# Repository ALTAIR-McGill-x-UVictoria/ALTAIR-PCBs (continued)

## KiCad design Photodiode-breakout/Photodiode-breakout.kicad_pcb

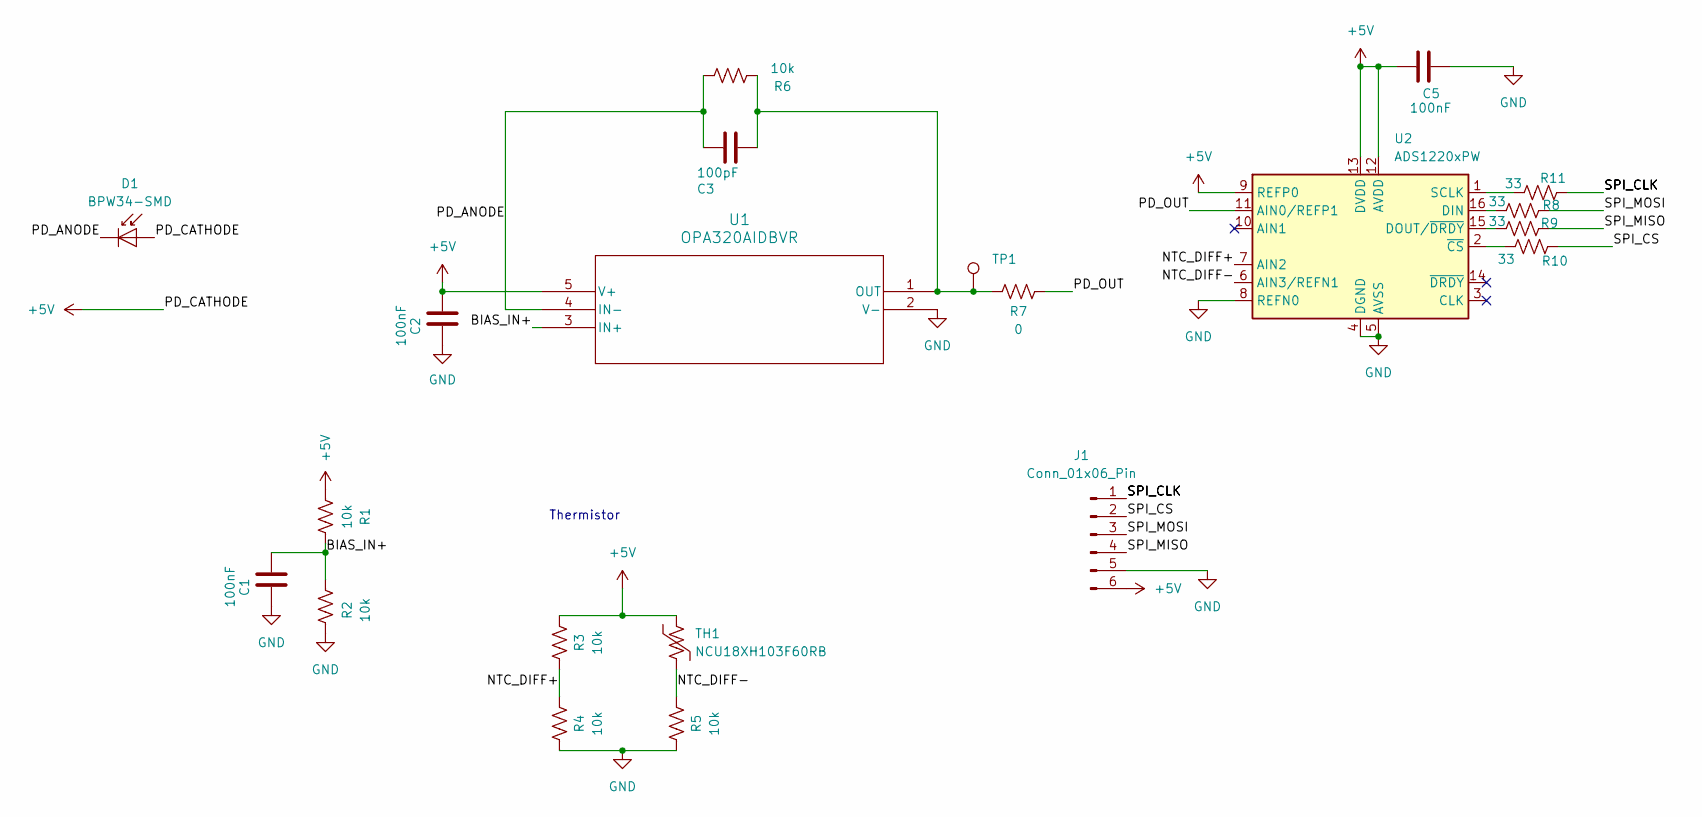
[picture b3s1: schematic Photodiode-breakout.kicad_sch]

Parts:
C1, C2, C5: 100nF; C_0603_1608Metric
C3: 100pF; C_0603_1608Metric
D1: BPW34-SMD; Osram_BPW34S-SMD
J1: Conn_01x06_Pin; JST_GH_BM06B-GHS-TBT_1x06-1MP_P1.25mm_Vertical
R1, R2, R3, R4, R5, R6: 10k; R_0603_1608Metric
R7: 0; R_0603_1608Metric
R8, R9, R10, R11: 33; R_0603_1608Metric
TH1: NCU18XH103F60RB; R_0603_1608Metric
TP1: TestPoint; PinHeader_1x01_P2.54mm_Vertical
U1: OPA320AIDBVR; DBV5
U2: ADS1220xPW; TSSOP-16_4.4x5mm_P0.65mm

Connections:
+5V: C2.1, C5.1, D1.2 (A), J1.6, R1.1, R3.2, TH1.1, U1.5 (V+), U2.9 (REFP0), U2.12 (AVDD), U2.13 (DVDD)
/BIAS_IN+: C1.1, R1.2, R2.2, U1.3 (IN+)
/NTC_DIFF+: R3.1, R4.2, U2.7 (AIN2)
/NTC_DIFF-: R5.2, TH1.2, U2.6 (AIN3/REFN1)
/PD_ANODE: C3.1, D1.1 (K), R6.2, U1.4 (IN-)
/PD_OUT: R7.2, U2.11 (AIN0/REFP1)
/SPI_CLK: J1.1, R11.1
/SPI_CS: J1.2, R10.1
/SPI_MISO: J1.4, R9.1
/SPI_MOSI: J1.3, R8.1
GND: C1.2, C2.2, C5.2, J1.5, R2.1, R4.1, R5.1, U1.2 (V-), U2.4 (DGND), U2.5 (AVSS), U2.8 (REFN0)
unnamed: C3.2, R6.1, R7.1, TP1.1 (1_1), U1.1 (OUT)
unnamed: R8.2, U2.16 (DIN)
unnamed: R9.2, U2.15 (DOUT/~DRDY)
unnamed: R11.2, U2.1 (SCLK)
unnamed: R10.2, U2.2 (~CS)

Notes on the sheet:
Thermistor

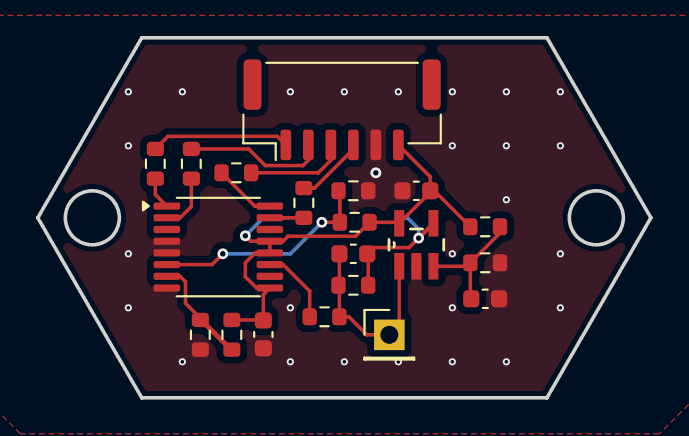
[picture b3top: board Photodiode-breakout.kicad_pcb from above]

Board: 2 copper layers, 34.1 x 20.0 mm, 21 parts (1 on the bottom side), 16 nets.

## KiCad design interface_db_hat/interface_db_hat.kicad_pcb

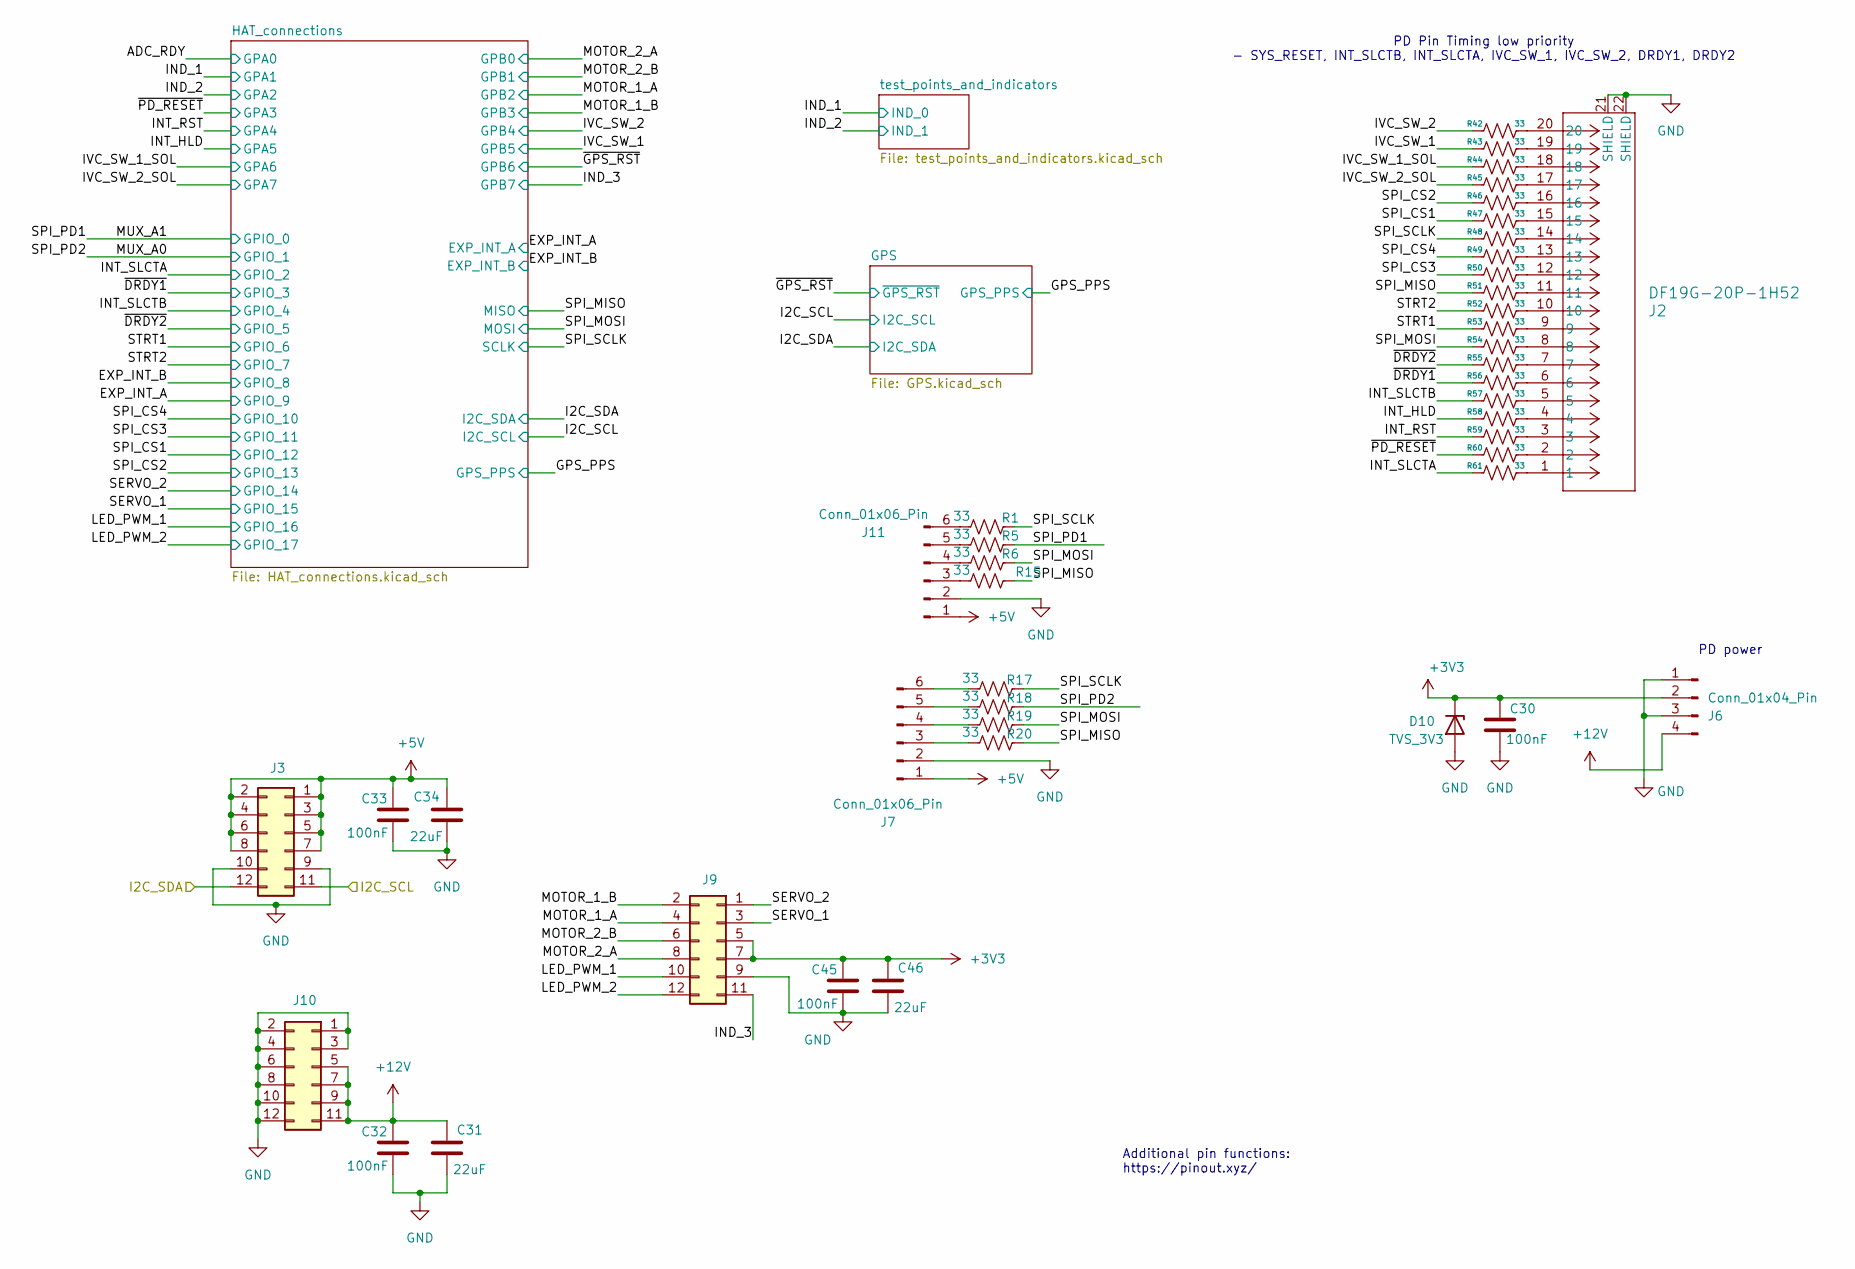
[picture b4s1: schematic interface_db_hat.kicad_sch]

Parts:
C30, C32, C33, C45: 100nF; C_0603_1608Metric_Pad1.08x0.95mm_HandSolder
C31, C34, C46: 22uF; C_0805_2012Metric
D10: TVS_3V3; D_0603_1608Metric
J2: DF19G-20P-1H52; CONN20_DF19G_HIR
J3, J9, J10: Conn_02x06_Counter_Clockwise; PinSocket_2x06_P2.54mm_Vertical
J6: Conn_01x04_Pin; JST_SH_SM04B-SRSS-TB_1x04-1MP_P1.00mm_Horizontal
J7, J11: Conn_01x06_Pin; JST_GH_SM06B-GHS-TB_1x06-1MP_P1.25mm_Horizontal
R1, R5, R6, R15, R17, R18, R19, R20: 33; R_0603_1608Metric
R42, R43, R44, R45, R46, R47, R48, R49, R50, R51, R52, R53, R54, R55, R56, R57, R58, R59, R60, R61: 33; R_0603_1608Metric_Pad0.98x0.95mm_HandSolder

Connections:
+3V3: C30.1, C45.2, C46.1, D10.1 (K), J6.2, J9.5, J9.7; also elsewhere on the board
+5V: C33.2, C34.1, J3.1, J3.2, J3.3, J3.4, J3.5, J3.6, J3.7, J3.8, J7.1, J11.1; also elsewhere on the board
+12V: C31.1, C32.2, J6.4, J10.5, J10.7, J10.9, J10.11; also elsewhere on the board
/I2C_SCL: J3.11; also elsewhere on the board
/I2C_SDA: J3.12; also elsewhere on the board
/IND_3: J9.11; also elsewhere on the board
/INT_HLD: R58.1; also elsewhere on the board
/INT_RST: R59.1; also elsewhere on the board
/INT_SLCTA: R61.1; also elsewhere on the board
/INT_SLCTB: R57.1; also elsewhere on the board
/IVC_SW_1: R43.1; also elsewhere on the board
/IVC_SW_1_SOL: R44.1; also elsewhere on the board
/IVC_SW_2: R42.1; also elsewhere on the board
/IVC_SW_2_SOL: R45.1; also elsewhere on the board
/LED_PWM_1: J9.10; also elsewhere on the board
/LED_PWM_2: J9.12; also elsewhere on the board
/MOTOR_1_A: J9.4; also elsewhere on the board
/MOTOR_1_B: J9.2; also elsewhere on the board
/MOTOR_2_A: J9.8; also elsewhere on the board
/MOTOR_2_B: J9.6; also elsewhere on the board
/MUX_A0: R18.1; also elsewhere on the board
/MUX_A1: R5.1; also elsewhere on the board
/SERVO_1: J9.3; also elsewhere on the board
/SERVO_2: J9.1; also elsewhere on the board
/SPI_CS1: R47.1; also elsewhere on the board
/SPI_CS2: R46.1; also elsewhere on the board
/SPI_CS3: R50.1; also elsewhere on the board
/SPI_CS4: R49.1; also elsewhere on the board
/SPI_MISO: R15.1, R20.1, R51.1; also elsewhere on the board
/SPI_MOSI: R6.1, R19.1, R54.1; also elsewhere on the board
/SPI_SCLK: R1.1, R17.1, R48.1; also elsewhere on the board
/STRT1: R53.1; also elsewhere on the board
/STRT2: R52.1; also elsewhere on the board
/~DRDY1: R56.1; also elsewhere on the board
/~DRDY2: R55.1; also elsewhere on the board
/~PD_RESET: R60.1; also elsewhere on the board
GND: C30.2, C31.2, C32.1, C33.1, C34.2, C45.1, C46.2, D10.2 (A), J2.21 (SHIELD), J2.22 (SHIELD), J3.9, J3.10, J6.1, J6.3, J7.2, J9.9, J10.1, J10.2, J10.3, J10.4, J10.6, J10.8, J10.10, J10.12, J11.2; also elsewhere on the board
unnamed: J2.1, R61.2
unnamed: J2.2, R60.2
unnamed: J2.3, R59.2
unnamed: J2.4, R58.2
unnamed: J2.5, R57.2
unnamed: J2.6, R56.2
unnamed: J2.7, R55.2
unnamed: J2.8, R54.2
unnamed: J2.9, R53.2
unnamed: J2.10, R52.2
unnamed: J2.11, R51.2
unnamed: J2.12, R50.2
unnamed: J2.13, R49.2
unnamed: J2.14, R48.2
unnamed: J2.15, R47.2
unnamed: J2.16, R46.2
unnamed: J2.17, R45.2
unnamed: J2.18, R44.2
unnamed: J2.19, R43.2
unnamed: J2.20, R42.2
unnamed: J7.3, R20.2
unnamed: J7.4, R19.2
unnamed: J7.5, R18.2
unnamed: J7.6, R17.2
unnamed: J11.3, R15.2
unnamed: J11.4, R6.2
unnamed: J11.5, R5.2
unnamed: J11.6, R1.2

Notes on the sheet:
PD power
Additional pin functions: https://pinout.xyz/
PD Pin Timing low priority - SYS_RESET, INT_SLCTB, INT_SLCTA, IVC_SW_1, IVC_SW_2, DRDY1, DRDY2

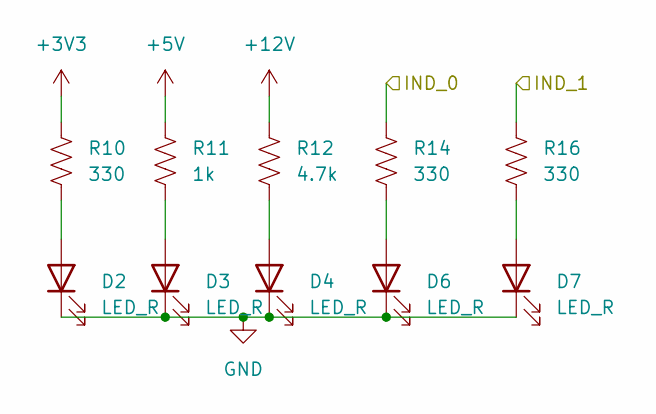
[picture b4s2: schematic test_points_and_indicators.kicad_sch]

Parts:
D2, D3, D4, D6, D7: LED_R; LED_0603_1608Metric_Pad1.05x0.95mm_HandSolder
R10, R14, R16: 330; R_0603_1608Metric_Pad0.98x0.95mm_HandSolder
R11: 1k; R_0603_1608Metric_Pad0.98x0.95mm_HandSolder
R12: 4.7k; R_0603_1608Metric_Pad0.98x0.95mm_HandSolder

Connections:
+3V3: R10.1; also elsewhere on the board
+5V: R11.1; also elsewhere on the board
+12V: R12.1; also elsewhere on the board
/IND_1: R14.1; also elsewhere on the board
/IND_2: R16.1; also elsewhere on the board
GND: D2.1 (K), D3.1 (K), D4.1 (K), D6.1 (K), D7.1 (K); also elsewhere on the board
unnamed: D2.2 (A), R10.2
unnamed: D3.2 (A), R11.2
unnamed: D4.2 (A), R12.2
unnamed: D6.2 (A), R14.2
unnamed: D7.2 (A), R16.2

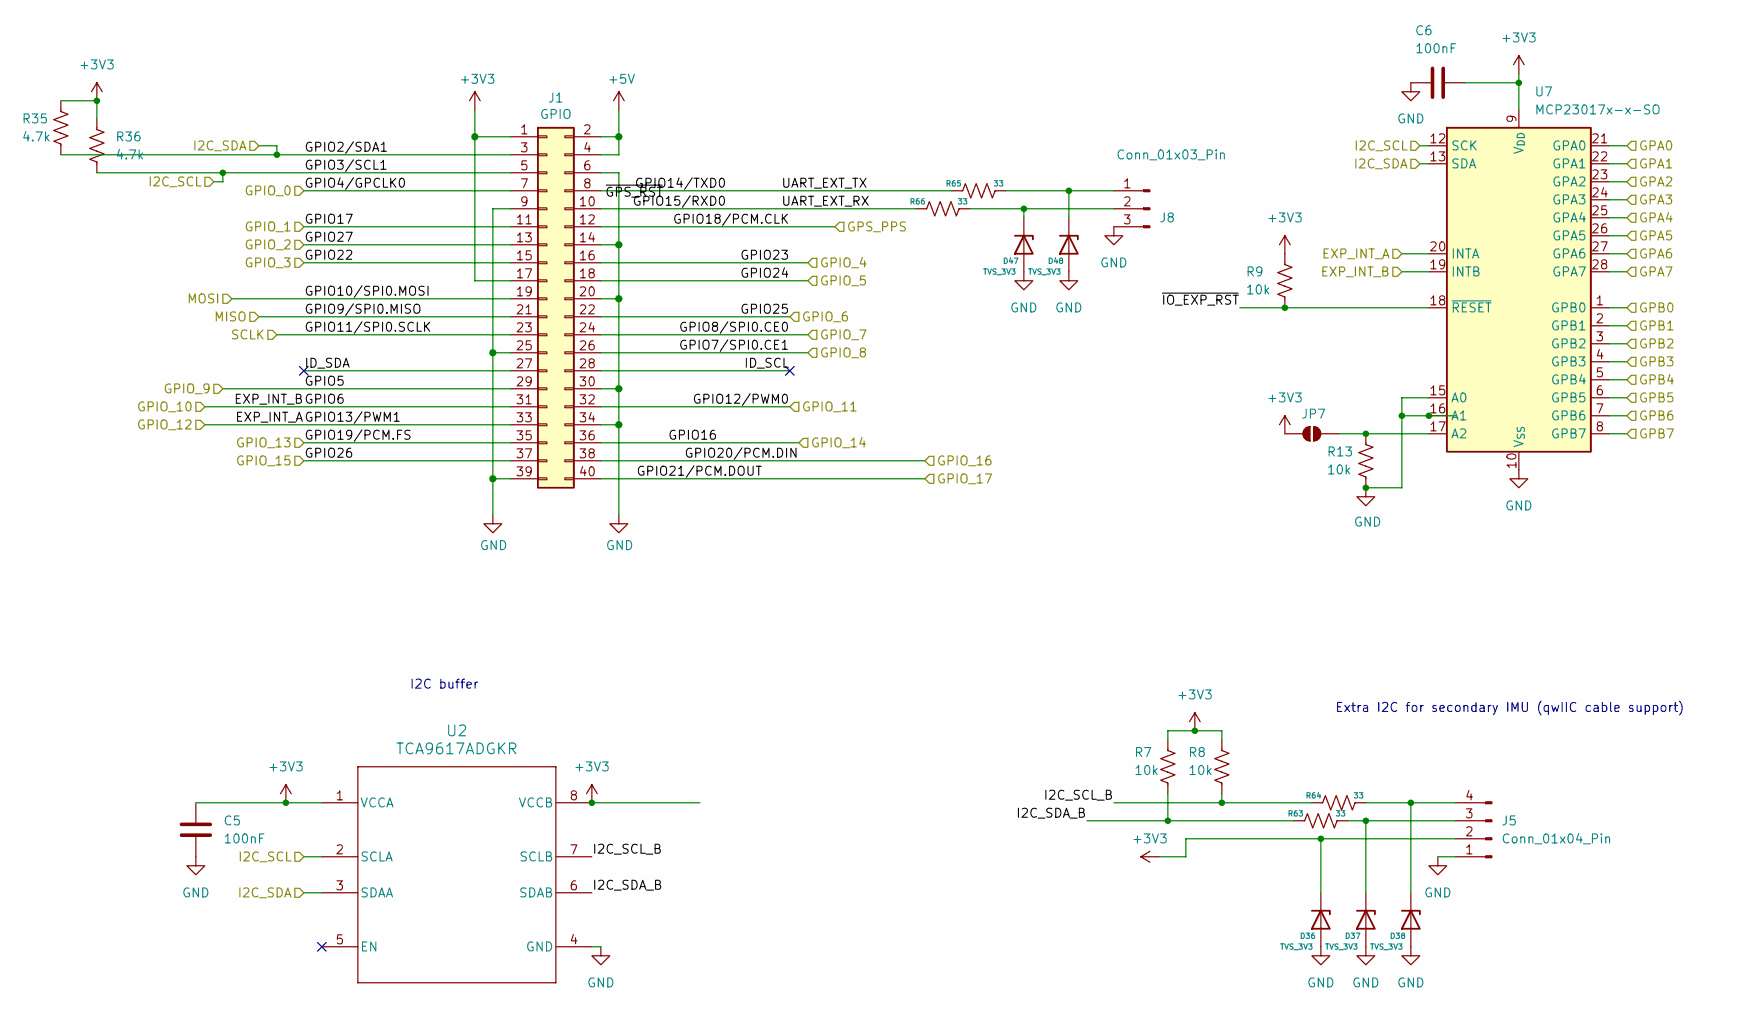
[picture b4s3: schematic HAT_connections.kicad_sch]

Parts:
C5, C6: 100nF; C_0603_1608Metric_Pad1.08x0.95mm_HandSolder
D36, D37, D38, D47, D48: TVS_3V3; D_0603_1608Metric
J1: GPIO; PinSocket_2x20_P2.54mm_Vertical
J5: Conn_01x04_Pin; JST_SH_SM04B-SRSS-TB_1x04-1MP_P1.00mm_Horizontal
J8: Conn_01x03_Pin; PinHeader_1x03_P2.54mm_Horizontal
JP7: SolderJumper_2_Open; SolderJumper-2_P1.3mm_Open_TrianglePad1.0x1.5mm
R7, R8, R9, R13: 10k; R_0603_1608Metric_Pad0.98x0.95mm_HandSolder
R35, R36: 4.7k; R_0603_1608Metric_Pad0.98x0.95mm_HandSolder
R63, R64, R65, R66: 33; R_0603_1608Metric_Pad0.98x0.95mm_HandSolder
U2: TCA9617ADGKR; DGK0008A
U7: MCP23017x-x-SO; SOIC-28W_7.5x17.9mm_P1.27mm

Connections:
+3V3: C5.1, C6.2, D36.1 (K), J1.1, J1.17, J5.2, JP7.2 (B), R7.1, R8.1, R9.2, R35.1, R36.1, U2.1 (VCCA), U2.8 (VCCB), U7.9 (V_{DD}); also elsewhere on the board
+5V: J1.2, J1.4; also elsewhere on the board
/ADC_RDY: U7.21 (GPA0)
/EXP_INT_A: J1.29, U7.20 (INTA)
/EXP_INT_B: J1.26, U7.19 (INTB)
/GPS_PPS: J1.12; also elsewhere on the board
/HAT_connections/GPIO14/TXD0: J1.8, R65.1
/HAT_connections/GPIO15/RXD0: J1.10, R66.1
/HAT_connections/I2C_SCL_B: R8.2, R64.1, U2.7 (SCLB)
/HAT_connections/I2C_SDA_B: R7.2, R63.1, U2.6 (SDAB)
/HAT_connections/ID_SCL: J1.28
/HAT_connections/ID_SDA: J1.27
/HAT_connections/~IO_EXP_RST: R9.1, U7.18 (~RESET)
/I2C_SCL: J1.5, R36.2, U2.2 (SCLA), U7.12 (SCK); also elsewhere on the board
/I2C_SDA: J1.3, R35.2, U2.3 (SDAA), U7.13 (SDA); also elsewhere on the board
/IND_1: U7.22 (GPA1); also elsewhere on the board
/IND_2: U7.23 (GPA2); also elsewhere on the board
/IND_3: U7.8 (GPB7); also elsewhere on the board
/INT_HLD: U7.26 (GPA5); also elsewhere on the board
/INT_RST: U7.25 (GPA4); also elsewhere on the board
/INT_SLCTA: J1.13; also elsewhere on the board
/INT_SLCTB: J1.16; also elsewhere on the board
/IVC_SW_1: U7.6 (GPB5); also elsewhere on the board
/IVC_SW_1_SOL: U7.27 (GPA6); also elsewhere on the board
/IVC_SW_2: U7.5 (GPB4); also elsewhere on the board
/IVC_SW_2_SOL: U7.28 (GPA7); also elsewhere on the board
/LED_PWM_1: J1.38; also elsewhere on the board
/LED_PWM_2: J1.40; also elsewhere on the board
/MOTOR_1_A: U7.3 (GPB2); also elsewhere on the board
/MOTOR_1_B: U7.4 (GPB3); also elsewhere on the board
/MOTOR_2_A: U7.1 (GPB0); also elsewhere on the board
/MOTOR_2_B: U7.2 (GPB1); also elsewhere on the board
/MUX_A0: J1.11; also elsewhere on the board
/MUX_A1: J1.7; also elsewhere on the board
/SERVO_1: J1.37; also elsewhere on the board
/SERVO_2: J1.36; also elsewhere on the board
/SPI_CS1: J1.33; also elsewhere on the board
/SPI_CS2: J1.35; also elsewhere on the board
/SPI_CS3: J1.32; also elsewhere on the board
/SPI_CS4: J1.31; also elsewhere on the board
/SPI_MISO: J1.21; also elsewhere on the board
/SPI_MOSI: J1.19; also elsewhere on the board
/SPI_SCLK: J1.23; also elsewhere on the board
/STRT1: J1.22; also elsewhere on the board
/STRT2: J1.24; also elsewhere on the board
/~DRDY1: J1.15; also elsewhere on the board
/~DRDY2: J1.18; also elsewhere on the board
/~GPS_RST: U7.7 (GPB6); also elsewhere on the board
/~PD_RESET: U7.24 (GPA3); also elsewhere on the board
GND: C5.2, C6.1, D36.2 (A), D37.2 (A), D38.2 (A), D47.2 (A), D48.2 (A), J1.6, J1.9, J1.14, J1.20, J1.25, J1.30, J1.34, J1.39, J5.1, J8.3, R13.1, U2.4 (GND), U7.10 (V_{SS}), U7.15 (A0), U7.16 (A1); also elsewhere on the board
unnamed: D37.1 (K), J5.3, R63.2
unnamed: D38.1 (K), J5.4, R64.2
unnamed: D47.1 (K), J8.2, R66.2
unnamed: D48.1 (K), J8.1, R65.2
unnamed: JP7.1 (A), R13.2, U7.17 (A2)

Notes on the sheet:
I2C buffer
Extra I2C for secondary IMU (qwIIC cable support)

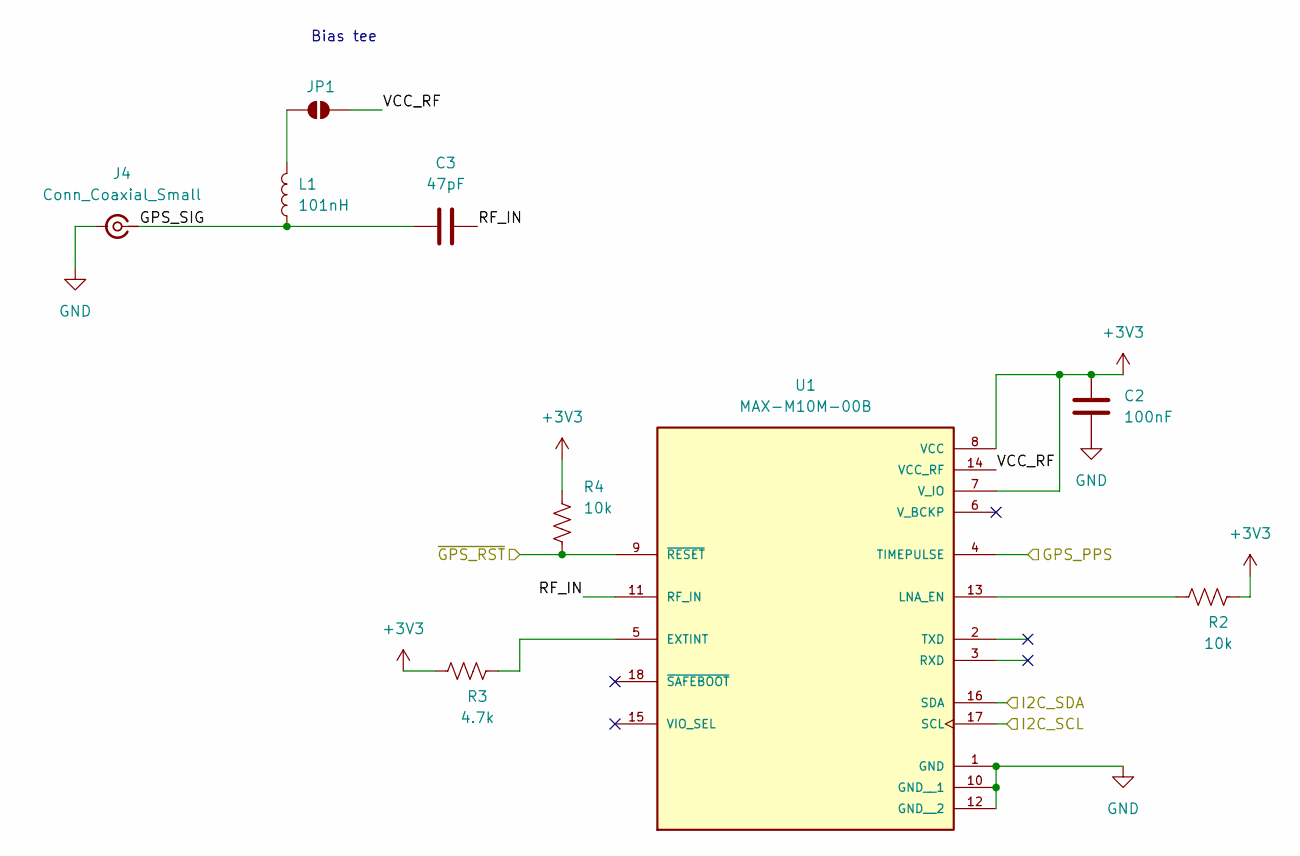
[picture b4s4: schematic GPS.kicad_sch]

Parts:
C2: 100nF; C_0603_1608Metric_Pad1.08x0.95mm_HandSolder
C3: 47pF; C_0402_1005Metric
J4: Conn_Coaxial_Small; SMA_Amphenol_132289_EdgeMount
JP1: SolderJumper_2_Open; SolderJumper-2_P1.3mm_Open_TrianglePad1.0x1.5mm
L1: 101nH; L_0402_1005Metric
R2, R4: 10k; R_0603_1608Metric_Pad0.98x0.95mm_HandSolder
R3: 4.7k; R_0603_1608Metric_Pad0.98x0.95mm_HandSolder
U1: MAX-M10M-00B; XCVR_MAX-M10M-00B; PARTREV C1

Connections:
+3V3: C2.1, R2.2, R3.1, R4.2, U1.7 (V_IO), U1.8 (VCC); also elsewhere on the board
/GPS/GPS_SIG: C3.2, J4.1 (In), L1.1
/GPS/RF_IN: C3.1, U1.11 (RF_IN)
/GPS/VCC_RF: JP1.1 (A), U1.14 (VCC_RF)
/GPS_PPS: U1.4 (TIMEPULSE); also elsewhere on the board
/I2C_SCL: U1.17 (SCL); also elsewhere on the board
/I2C_SDA: U1.16 (SDA); also elsewhere on the board
/~GPS_RST: R4.1, U1.9 (~RESET); also elsewhere on the board
GND: C2.2, J4.2 (Ext), U1.1 (GND), U1.10 (GND__1), U1.12 (GND__2); also elsewhere on the board
unnamed: JP1.2 (B), L1.2
unnamed: R3.2, U1.5 (EXTINT)
unnamed: R2.1, U1.13 (LNA_EN)

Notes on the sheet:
Bias tee

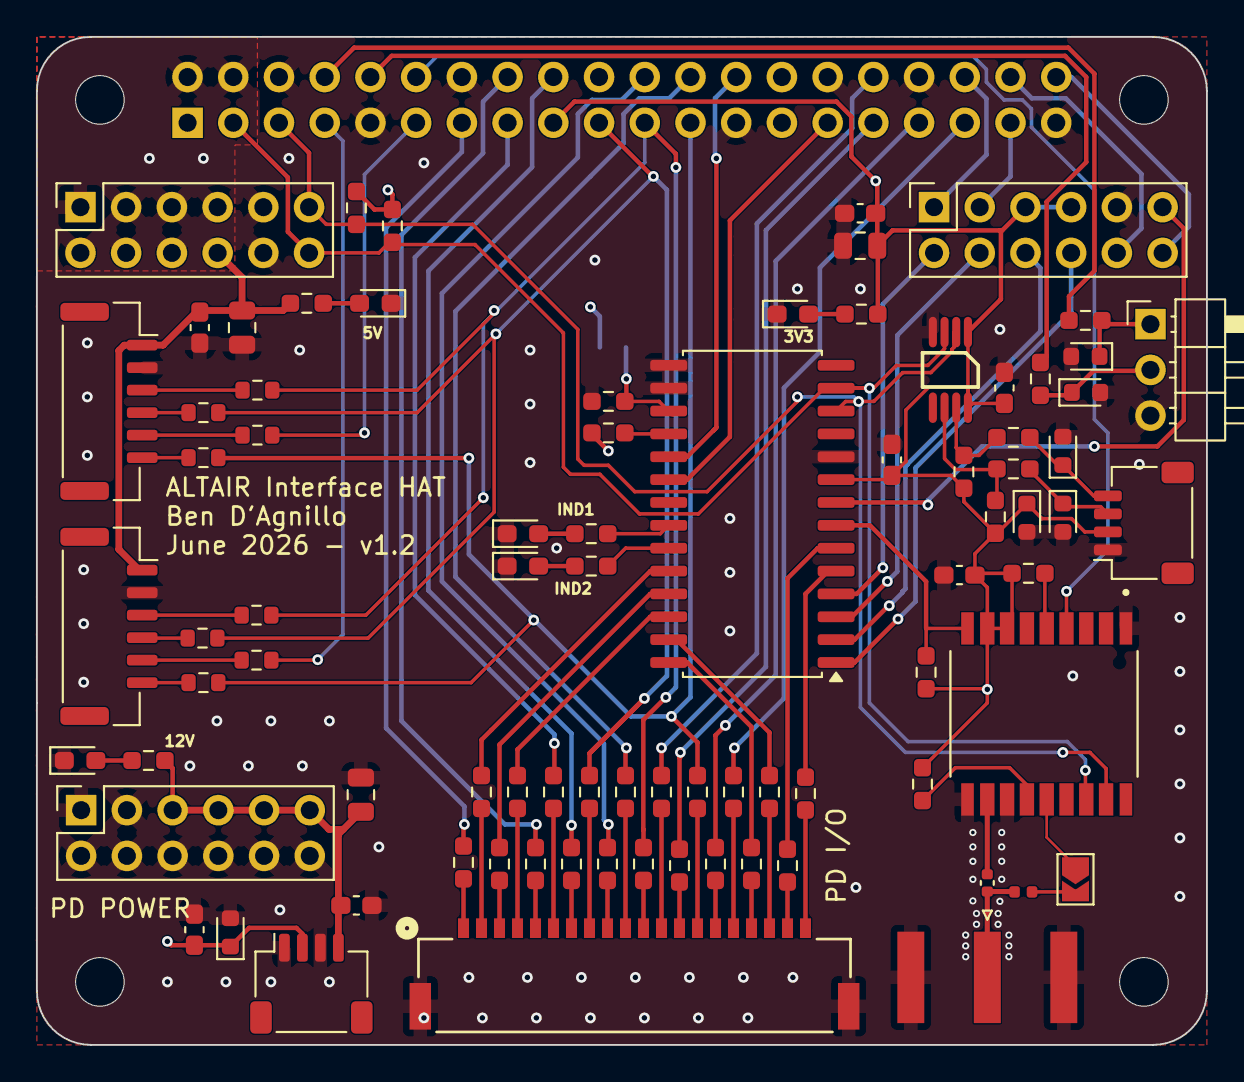
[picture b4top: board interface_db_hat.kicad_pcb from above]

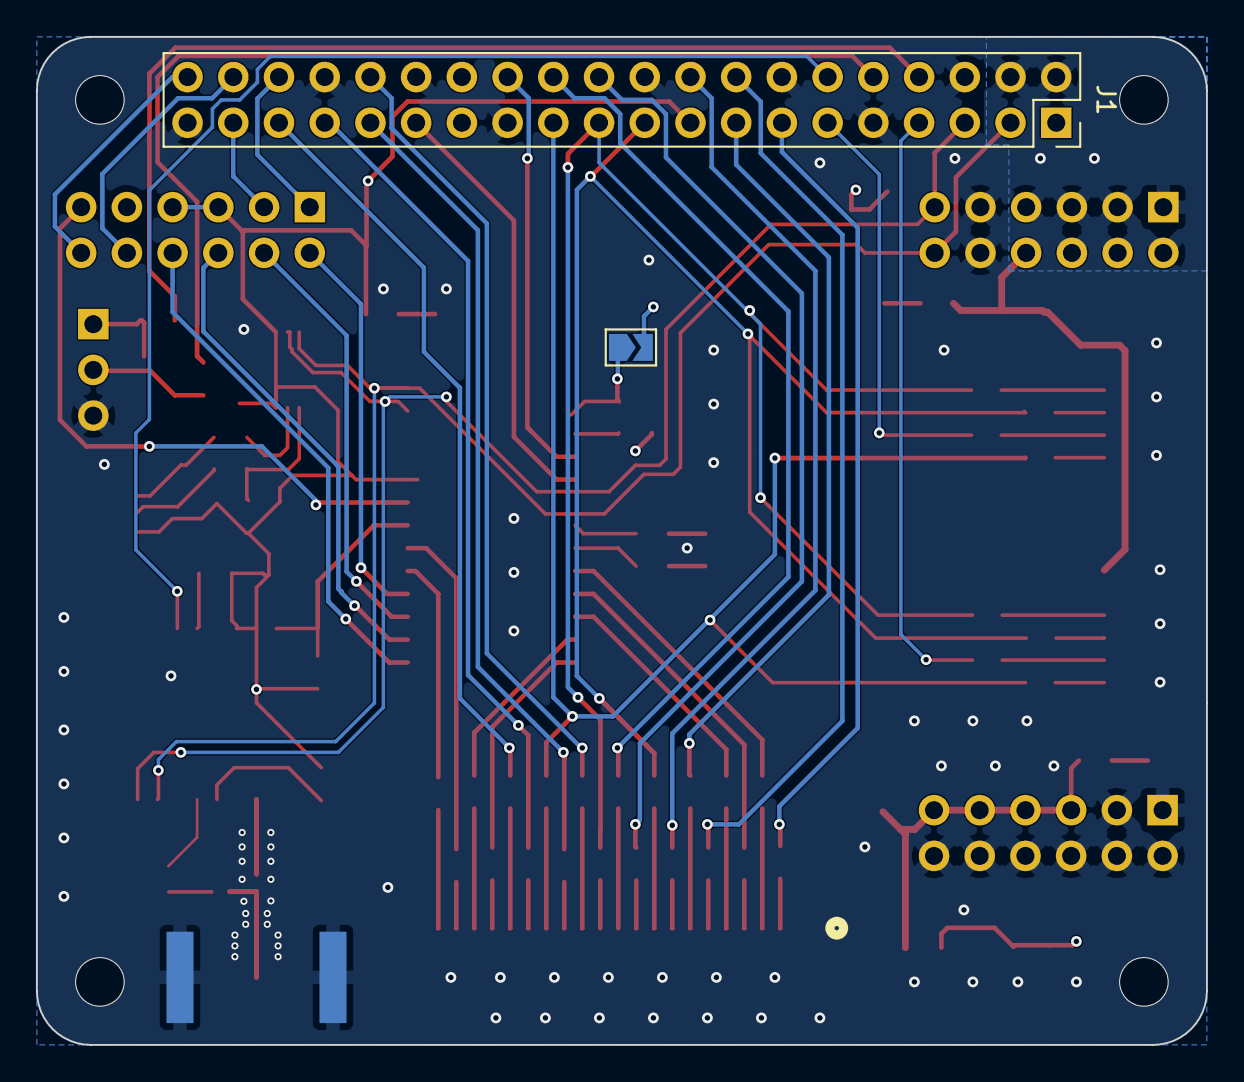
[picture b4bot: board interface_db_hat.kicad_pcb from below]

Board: 4 copper layers, 65.0 x 56.0 mm, 89 parts (2 on the bottom side), 92 nets.

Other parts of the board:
MH1, MH2, MH3, MH4: MountingHole_2.7mm_M2.5

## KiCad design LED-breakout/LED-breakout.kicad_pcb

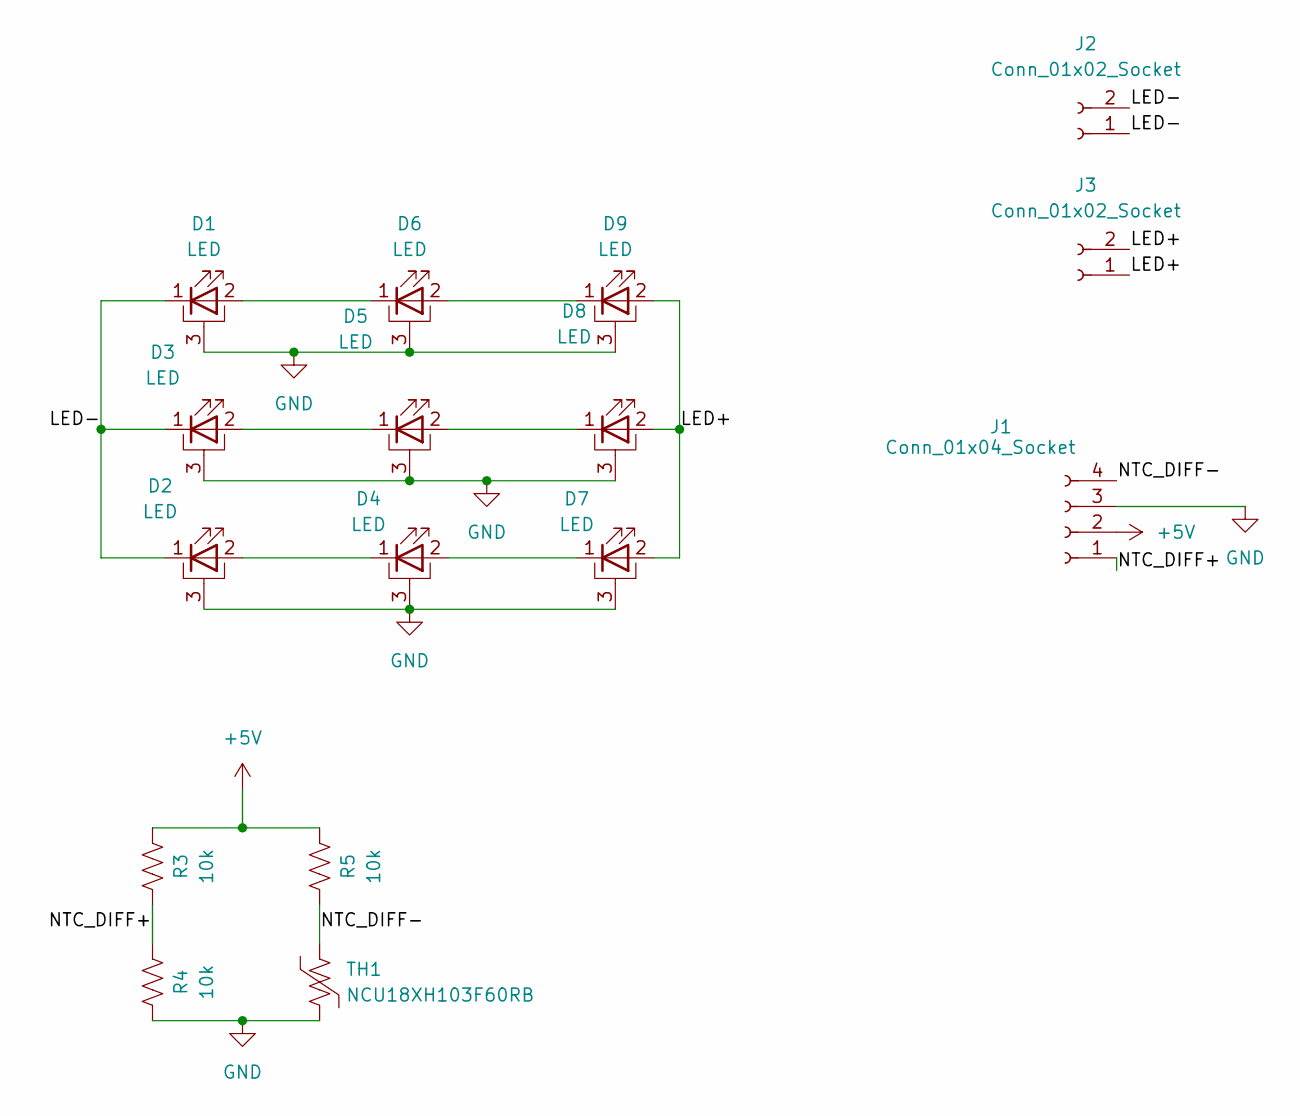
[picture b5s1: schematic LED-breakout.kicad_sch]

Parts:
D1, D2, D3, D4, D5, D6, D7, D8, D9: LED; LED_Cree-XP
J1: Conn_01x04_Socket; JST_GH_BM04B-GHS-TBT_1x04-1MP_P1.25mm_Vertical
J2, J3: Conn_01x02_Socket; JST_GH_BM02B-GHS-TBT_1x02-1MP_P1.25mm_Vertical
R3, R4, R5: 10k; R_0603_1608Metric
TH1: NCU18XH103F60RB; R_0603_1608Metric

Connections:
+5V: J1.2, R3.2, R5.2
/LED+: D7.2 (A), D8.2 (A), D9.2 (A), J3.1, J3.2
/LED-: D1.1 (K), D2.1 (K), D3.1 (K), J2.1, J2.2
/NTC_DIFF+: J1.1, R3.1, R4.2
/NTC_DIFF-: J1.4, R5.1, TH1.1
GND: D1.3 (PAD), D2.3 (PAD), D3.3 (PAD), D4.3 (PAD), D5.3 (PAD), D6.3 (PAD), D7.3 (PAD), D8.3 (PAD), D9.3 (PAD), J1.3, R4.1, TH1.2
unnamed: D1.2 (A), D6.1 (K)
unnamed: D2.2 (A), D4.1 (K)
unnamed: D3.2 (A), D5.1 (K)
unnamed: D4.2 (A), D7.1 (K)
unnamed: D5.2 (A), D8.1 (K)
unnamed: D6.2 (A), D9.1 (K)

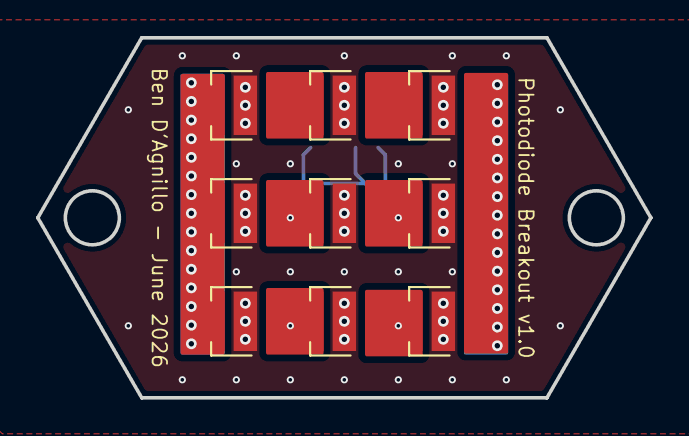
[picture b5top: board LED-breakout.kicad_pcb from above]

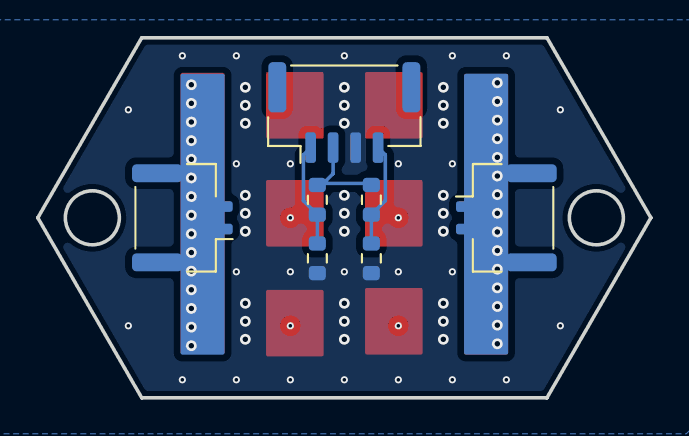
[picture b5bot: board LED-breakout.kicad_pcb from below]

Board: 2 copper layers, 34.1 x 20.0 mm, 16 parts (7 on the bottom side), 12 nets.
